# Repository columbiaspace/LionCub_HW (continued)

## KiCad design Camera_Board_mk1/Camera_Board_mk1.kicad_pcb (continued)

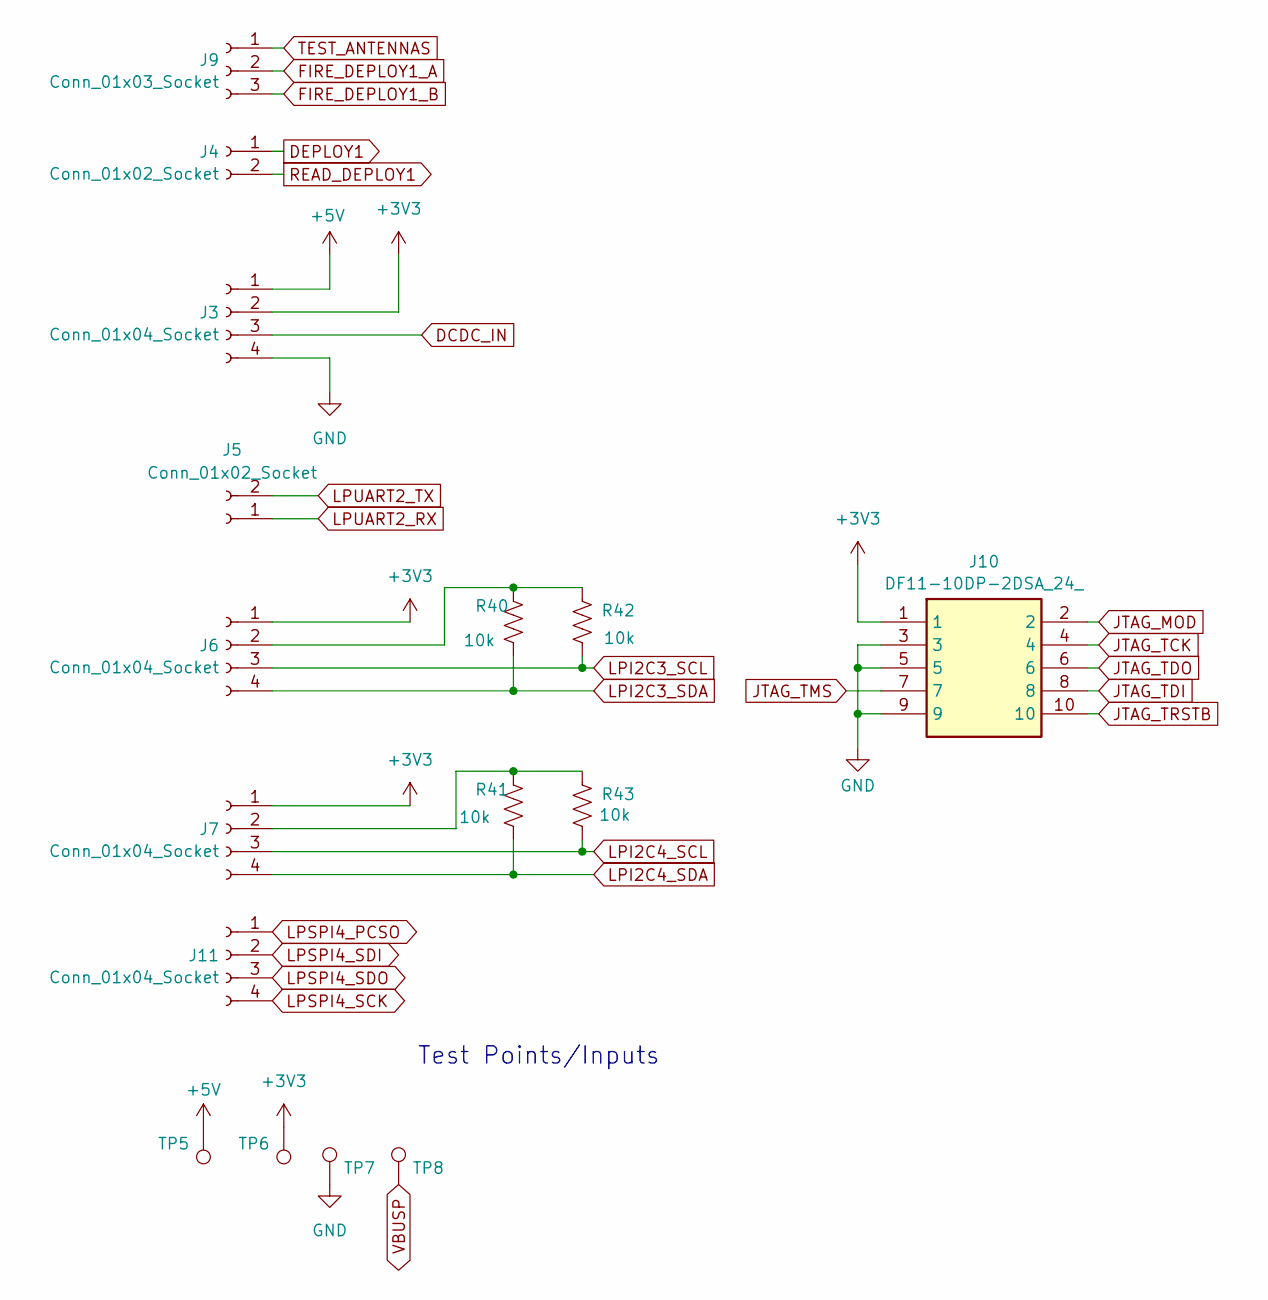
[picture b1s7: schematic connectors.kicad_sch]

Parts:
J3, J6, J7, J11: Conn_01x04_Socket; PinHeader_1x04_P2.54mm_Vertical
J4, J5: Conn_01x02_Socket; PinHeader_1x02_P2.54mm_Vertical
J9: Conn_01x03_Socket; PinHeader_1x03_P2.54mm_Vertical
J10: DF11-10DP-2DSA_24_; SHDR10W50P200_2X5_1200X500X660P; Manufacturer_Part_Number DF11-10DP-2DSA(24); Mouser Part Number 798-DF11-10DP-2DSA24
R40, R41, R42, R43: 10k; R_0201_0603Metric
TP5, TP6, TP7, TP8: TestPoint; TestPoint_Loop_D1.80mm_Drill1.0mm_Beaded

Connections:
+3V3: J3.2, J6.1, J7.1, J10.1, TP6.1; also elsewhere on the board
DCDC_IN: J3.3; also elsewhere on the board
DEPLOY1: J4.1; also elsewhere on the board
FIRE_DEPLOY1_A: J9.2; also elsewhere on the board
FIRE_DEPLOY1_B: J9.3; also elsewhere on the board
GND: J3.4, J10.3, J10.5, J10.9, TP7.1; also elsewhere on the board
JTAG_MOD: J10.2; also elsewhere on the board
JTAG_TCK: J10.4; also elsewhere on the board
JTAG_TDI: J10.8; also elsewhere on the board
JTAG_TDO: J10.6; also elsewhere on the board
JTAG_TMS: J10.7; also elsewhere on the board
JTAG_TRSTB: J10.10; also elsewhere on the board
LPI2C3_SCL: J6.3, R42.2; also elsewhere on the board
LPI2C3_SDA: J6.4, R40.2; also elsewhere on the board
LPI2C4_SCL: J7.3, R43.2; also elsewhere on the board
LPI2C4_SDA: J7.4, R41.2; also elsewhere on the board
LPSPI4_PCSO: J11.1; also elsewhere on the board
LPSPI4_SCK: J11.4; also elsewhere on the board
LPSPI4_SDI: J11.2; also elsewhere on the board
LPSPI4_SDO: J11.3; also elsewhere on the board
LPUART2_RX: J5.1; also elsewhere on the board
LPUART2_TX: J5.2; also elsewhere on the board
unnamed: J6.2, R40.1, R42.1
unnamed: J7.2, R41.1, R43.1
READ_DEPLOY1: J4.2; also elsewhere on the board
TEST_ANTENNAS: J9.1; also elsewhere on the board
VBUS: J3.1, TP5.1; also elsewhere on the board
VBUSP: TP8.1; also elsewhere on the board

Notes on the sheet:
Test Points/Inputs

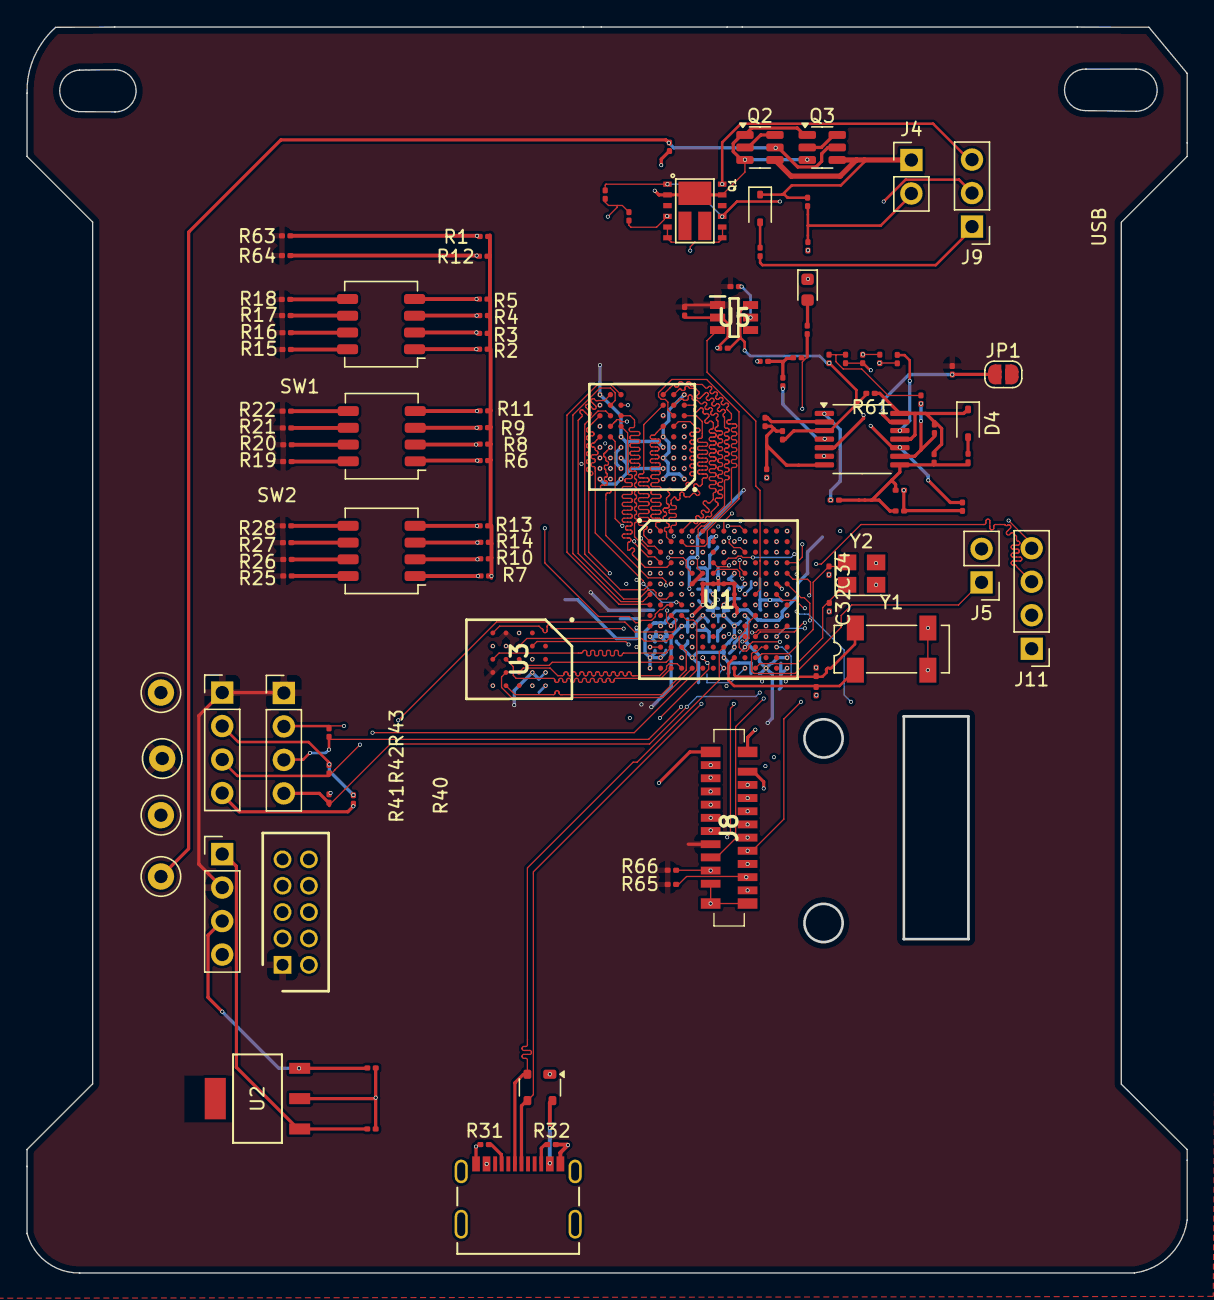
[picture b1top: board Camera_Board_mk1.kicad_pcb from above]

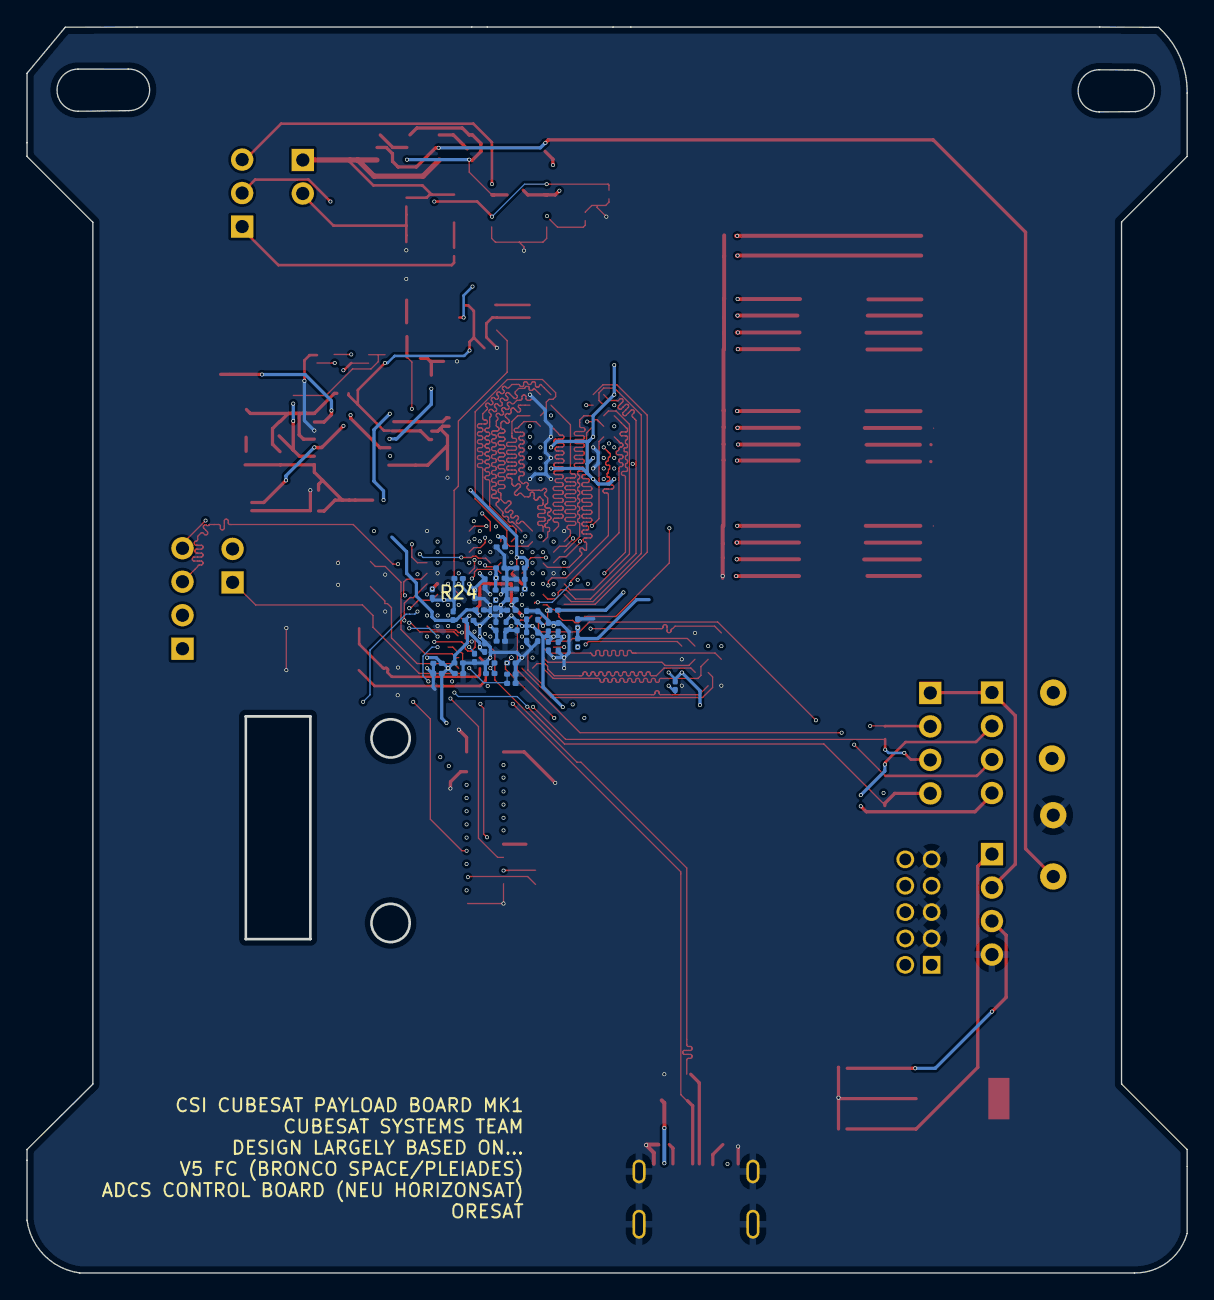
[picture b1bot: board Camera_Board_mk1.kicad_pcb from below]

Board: 4 copper layers, 88.0 x 94.5 mm, 150 parts (44 on the bottom side), 161 nets.

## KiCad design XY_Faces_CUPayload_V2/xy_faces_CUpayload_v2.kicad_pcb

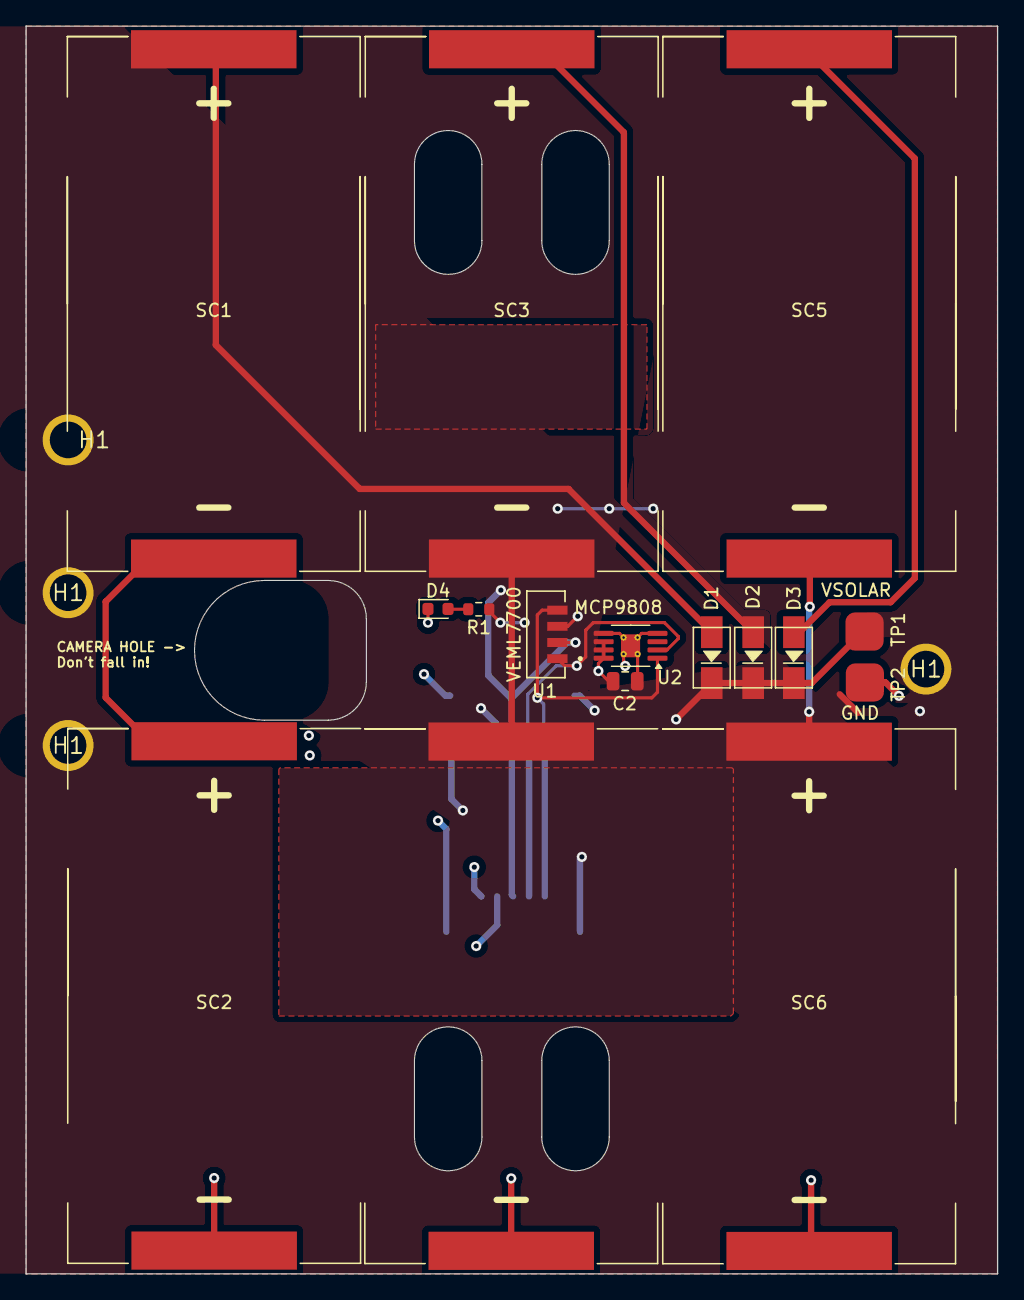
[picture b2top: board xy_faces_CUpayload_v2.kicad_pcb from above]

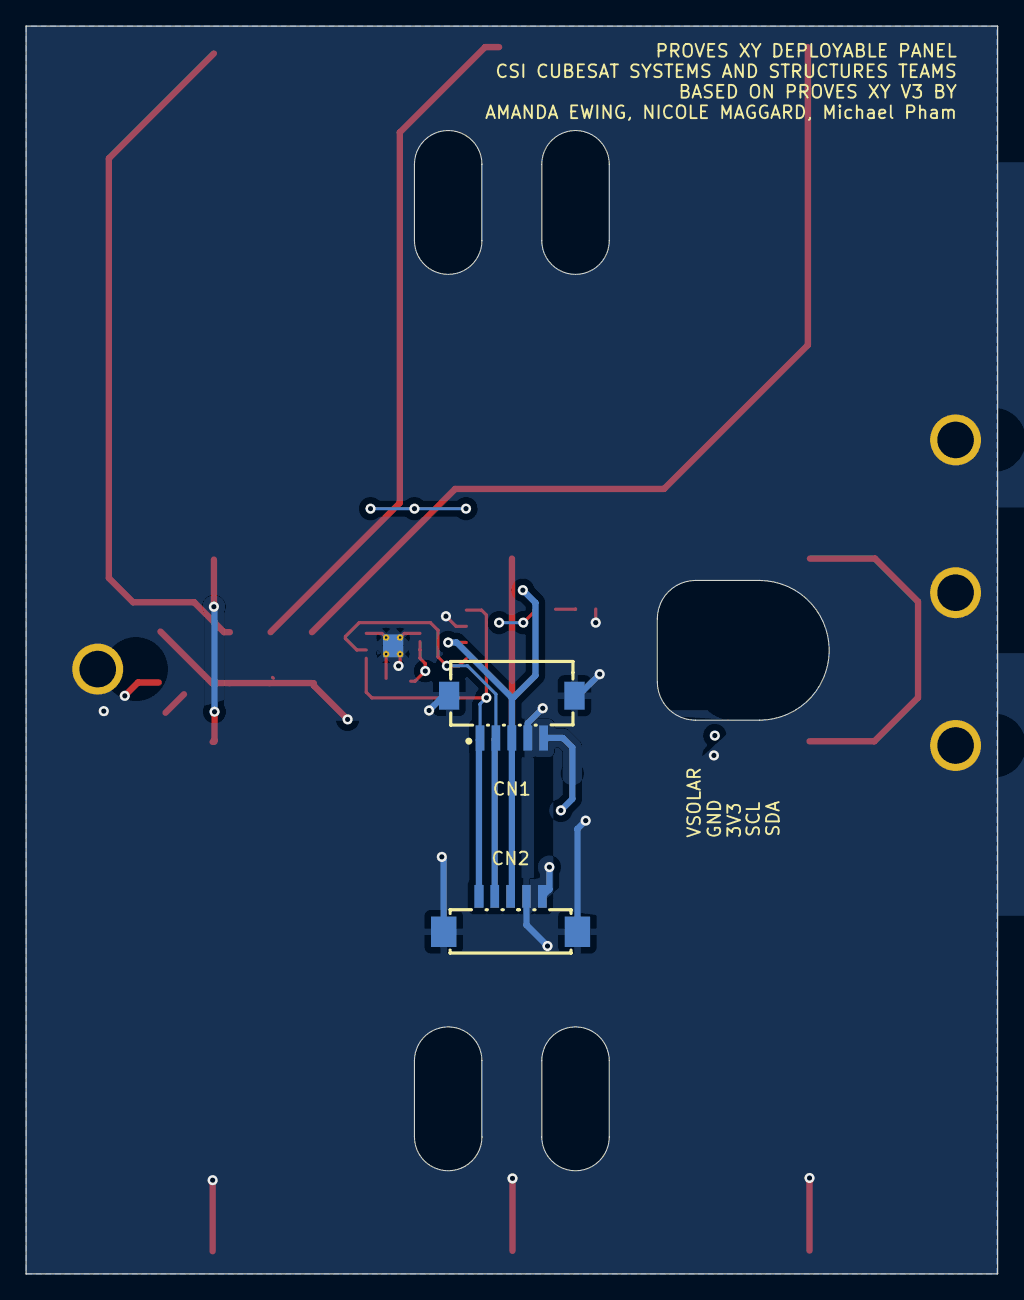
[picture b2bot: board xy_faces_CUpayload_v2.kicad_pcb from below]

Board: 4 copper layers, 76.3 x 98.0 mm, 22 parts (2 on the bottom side), 12 nets.

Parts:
C2: 1uF; C_0805_2012Metric
CN1: DF13A-5P-1.25H(21); CONN-SMD_5P-P1.25_HRS_DF13A-5P-1.25H
CN2: DF13C-5P-1.25V(21); CONN-SMD_DF13C-5P-1.25V-21
D1, D2, D3: CDBA240LL-HF; DO-214AC
D4: CQY99; LED_0603_1608Metric
H1, H1#2, H1#3, H1#4: MountingHole
R1: 1k; R_0603_1608Metric
SC1, SC2, SC3, SC4, SC5, SC6: SM101K07TF; KXOB101K08F-TR
TP1, TP2: TestPoint; Test Pad
U1: VEML7700; XDCR_VEML7700-TT
U2: MCP9808_DFN; MSOP-8-1EP_3x3mm_P0.65mm_EP1.5x1.8mm_ThermalVias

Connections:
+3V3: C2.1, CN1.3, CN2.3, R1.1, U1.2 (VDD), U2.6 (A1), U2.7 (A0), U2.8 (VDD)
GND: C2.2, CN1.4, CN1.6, CN1.7, CN2.4, CN2.6, CN2.7, D4.1 (K), SC2.2 (-), SC4.2 (-), SC6.2 (-), TP2.1, U1.3 (GND), U2.4 (GND), U2.5 (A2), U2.9 (EP/GND)
unnamed: D1.2 (A), SC1.1 (+)
unnamed: D2.2 (A), SC3.1 (+)
unnamed: D3.2 (A), SC5.1 (+)
unnamed: D4.2 (A), R1.2
unnamed: SC1.2 (-), SC2.1 (+)
unnamed: SC3.2 (-), SC4.1 (+)
unnamed: SC5.2 (-), SC6.1 (+)
SCL: CN1.2, CN2.2, U1.1 (SCL), U2.2 (SCL)
SDA: CN1.1, CN2.1, U1.4 (SDA), U2.1 (SDA)
VSOLAR: CN1.5, CN2.5, D1.1 (K), D2.1 (K), D3.1 (K), TP1.1

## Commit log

2025-04-16 Modified XY Solar Faces from Proves for Structures Team
2025-04-21 Created Camera Hole & Moved Diodes/Traces
    VSolar pad unconnected
2025-04-21 Removed Magnetorquer/Driver and Modified Routing/Text
2025-04-21 Fixed Change Issue
2025-04-21 3D Models and Fab Gerbers done
2025-04-30 Grounding pads for mounting holes
2025-05-10 Fabrication Model
2025-05-10 Added Camera Board (Payload Board) KiCad project
